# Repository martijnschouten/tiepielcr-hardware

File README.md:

# TiePieLCR hardware
Contains the design files of the TiePieLCR multi-frequency spectrometer front-end. The TiePieLCR consists of a TiePie engineering HS5 with custom PCB and a 3D printed case. The front-end contains an instrumentation amplifier to measure differential voltages, a transimpedance amplifier to measure currents and  voltage controlled current source to be able to do safe current controlled measurements on humans.

To make one of your own you can use the supplied gerber files to get a PCB fabricated. To make some improments to design you can open the schematic in Kicad. The STL's and Inventor files of the case for the electronics can also be found in this repository.

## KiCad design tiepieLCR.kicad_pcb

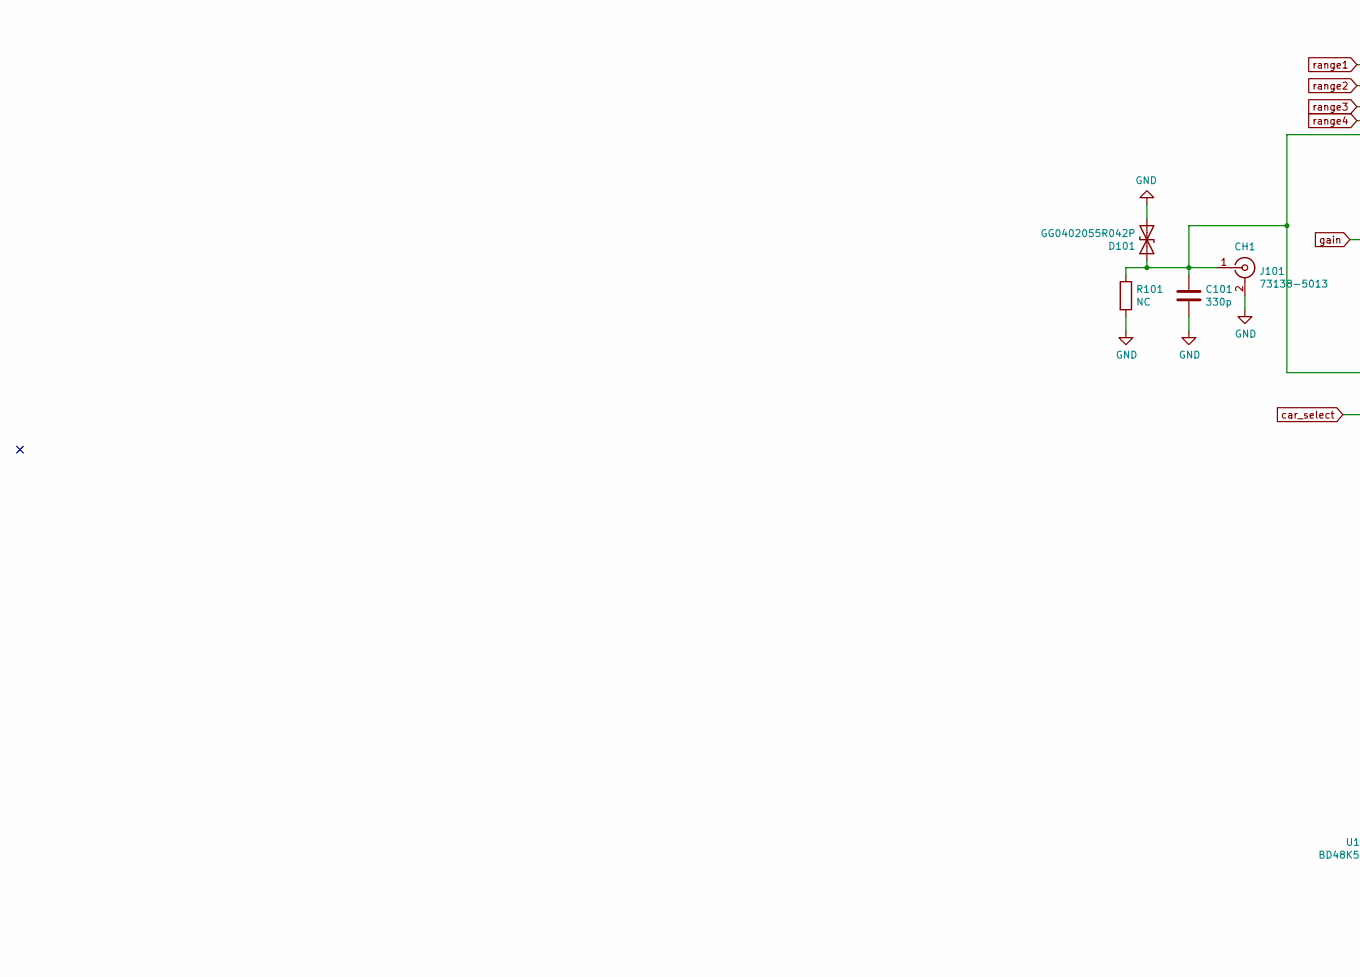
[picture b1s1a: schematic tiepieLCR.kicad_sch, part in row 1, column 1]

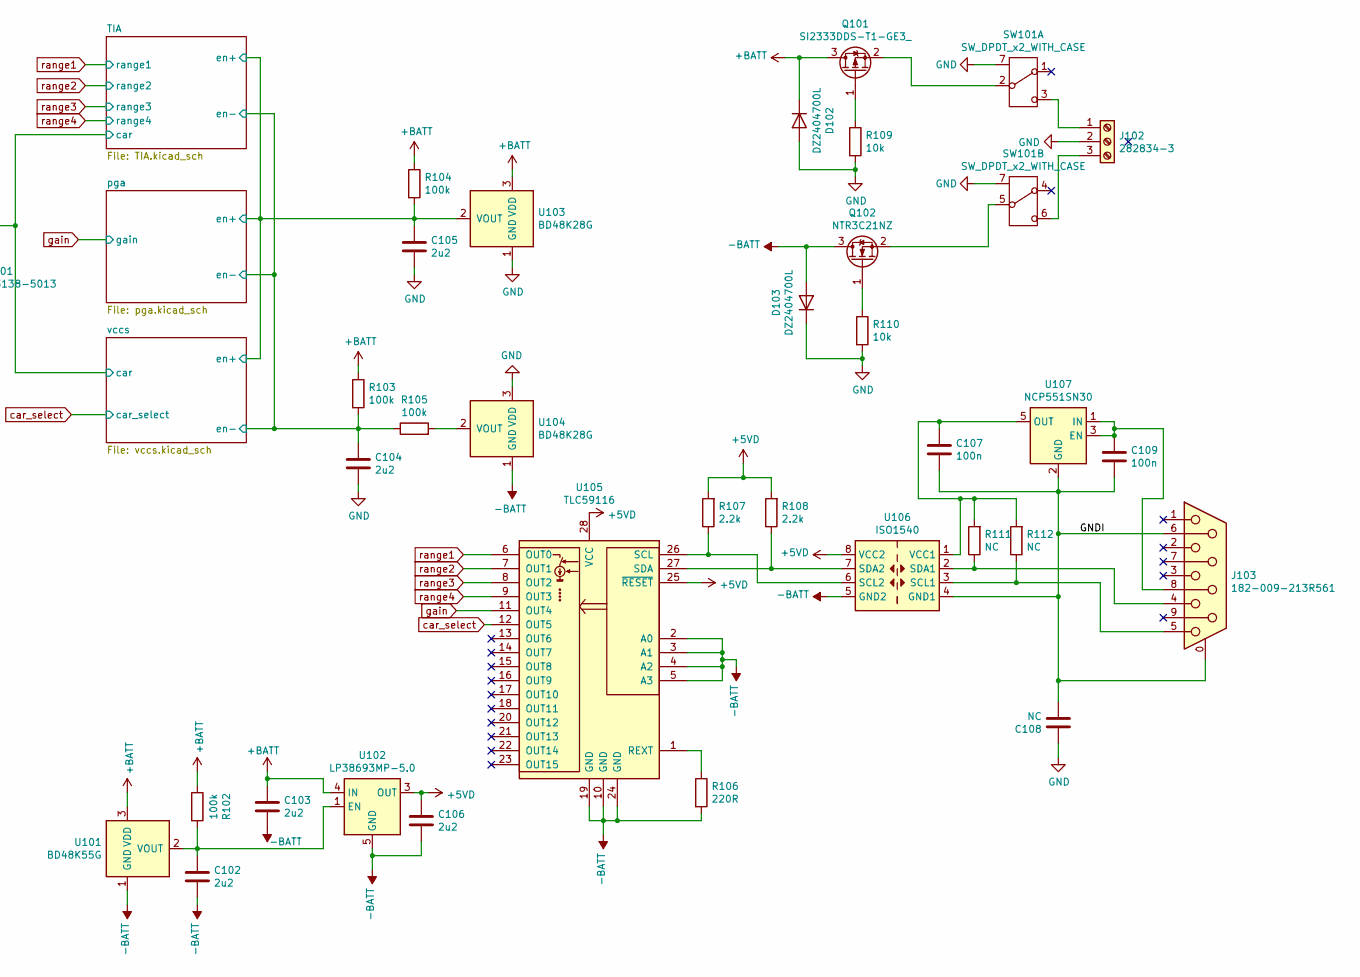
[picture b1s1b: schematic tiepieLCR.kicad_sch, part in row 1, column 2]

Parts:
C101: 330p; C_0603_1608Metric_Pad1.05x0.95mm_HandSolder
C102, C103, C104, C105, C106: 2u2; C_0603_1608Metric_Pad1.05x0.95mm_HandSolder
C107, C109: 100n; C_0603_1608Metric_Pad1.05x0.95mm_HandSolder
C108: NC; C_1206_3216Metric
D101: GG0402055R042P; D_0402_1005Metric
D102, D103: DZ2404700L; D_SOD-128
J101: 73138-5013; 0731385033
J102: 282834-3; TerminalBlock_TE_282834-3_1x03_P2.54mm_Horizontal
J103: 182-009-213R561; DSUB-9_Female_Horizontal_P2.77x2.84mm_EdgePinOffset7.70mm_H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
Q101: SI2333DDS-T1-GE3_; SOT-23
Q102: NTR3C21NZ; SOT-23
R101, R111, R112: NC; R_0603_1608Metric_Pad1.05x0.95mm_HandSolder
R102, R103, R104, R105: 100k; R_0603_1608Metric_Pad1.05x0.95mm_HandSolder
R106: 220R; R_0603_1608Metric_Pad1.05x0.95mm_HandSolder
R107, R108: 2.2k; R_0603_1608Metric_Pad1.05x0.95mm_HandSolder
R109, R110: 10k; R_0603_1608Metric_Pad1.05x0.95mm_HandSolder
SW101: SW_DPDT_x2_WITH_CASE; EG2219
U101: BD48K55G; SOT-23
U102: LP38693MP-5.0; SOT-223-5
U103, U104: BD48K28G; SOT-23
U105: TLC59116; TSSOP-28_4.4x9.7mm_P0.65mm
U106: ISO1540; SOIC-8_3.9x4.9mm_P1.27mm
U107: NCP551SN30; SOT-23-5

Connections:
+5VD: C106.1, R107.2, R108.2, U102.3 (OUT), U105.25 (~RESET), U105.28 (VCC), U106.8 (VCC2); also elsewhere on the board
+BATT: C103.1, D102.1 (K), Q101.3 (D), R102.1, R103.1, R104.1, U101.3 (VDD), U102.4 (IN), U103.3 (VDD); also elsewhere on the board
-BATT: C102.2, C103.2, C106.2, D103.2 (A), Q102.3 (D), R106.2, U101.1 (GND), U102.5 (GND), U104.1 (GND), U105.2 (A0), U105.3 (A1), U105.4 (A2), U105.5 (A3), U105.10 (GND), U105.19 (GND), U105.24 (GND), U106.5 (GND2); also elsewhere on the board
/GNDI: C107.2, C108.2, C109.2, J103.0 (PAD), J103.6 (GND), U106.4 (GND1), U107.2 (GND)
/TIA/car: C101.1, D101.1 (A1), J101.1 (In), R101.1; also elsewhere on the board
/TIA/en+: C105.1, R104.2, U103.2 (VOUT); also elsewhere on the board
/TIA/en-: C104.1, R103.2, R105.1; also elsewhere on the board
GND: C101.2, C104.2, C105.2, C108.1, D101.2 (A2), D102.2 (A), D103.1 (K), J101.2 (Ext), J102.2, R101.2, R109.2, R110.2, SW101.7 (CASE), U103.1 (GND), U104.3 (VDD); also elsewhere on the board
unnamed: C102.1, R102.2, U101.2 (VOUT), U102.1 (EN)
unnamed: C107.1, R111.2, R112.2, U106.1 (VCC1), U107.5 (OUT)
unnamed: C109.1, J103.8 (OUT), U107.1 (IN), U107.3 (EN)
unnamed: J102.1, SW101.3 (C)
unnamed: J102.3, SW101.6 (C)
unnamed: J103.4 (SDA), R111.1, U106.2 (SDA1)
unnamed: J103.5 (SCL), R112.1, U106.3 (SCL1)
unnamed: Q101.1 (G), R109.1
unnamed: Q101.2 (S), SW101.2 (B)
unnamed: Q102.1 (G), R110.1
unnamed: Q102.2 (S), SW101.5 (B)
unnamed: R105.2, U104.2 (VOUT)
unnamed: R106.1, U105.1 (REXT)
unnamed: R107.1, U105.26 (SCL), U106.6 (SCL2)
unnamed: R108.1, U105.27 (SDA), U106.7 (SDA2)
car_select: U105.12 (OUT5); also elsewhere on the board
gain: U105.11 (OUT4); also elsewhere on the board
range1: U105.6 (OUT0); also elsewhere on the board
range2: U105.7 (OUT1); also elsewhere on the board
range3: U105.8 (OUT2); also elsewhere on the board
range4: U105.9 (OUT3); also elsewhere on the board

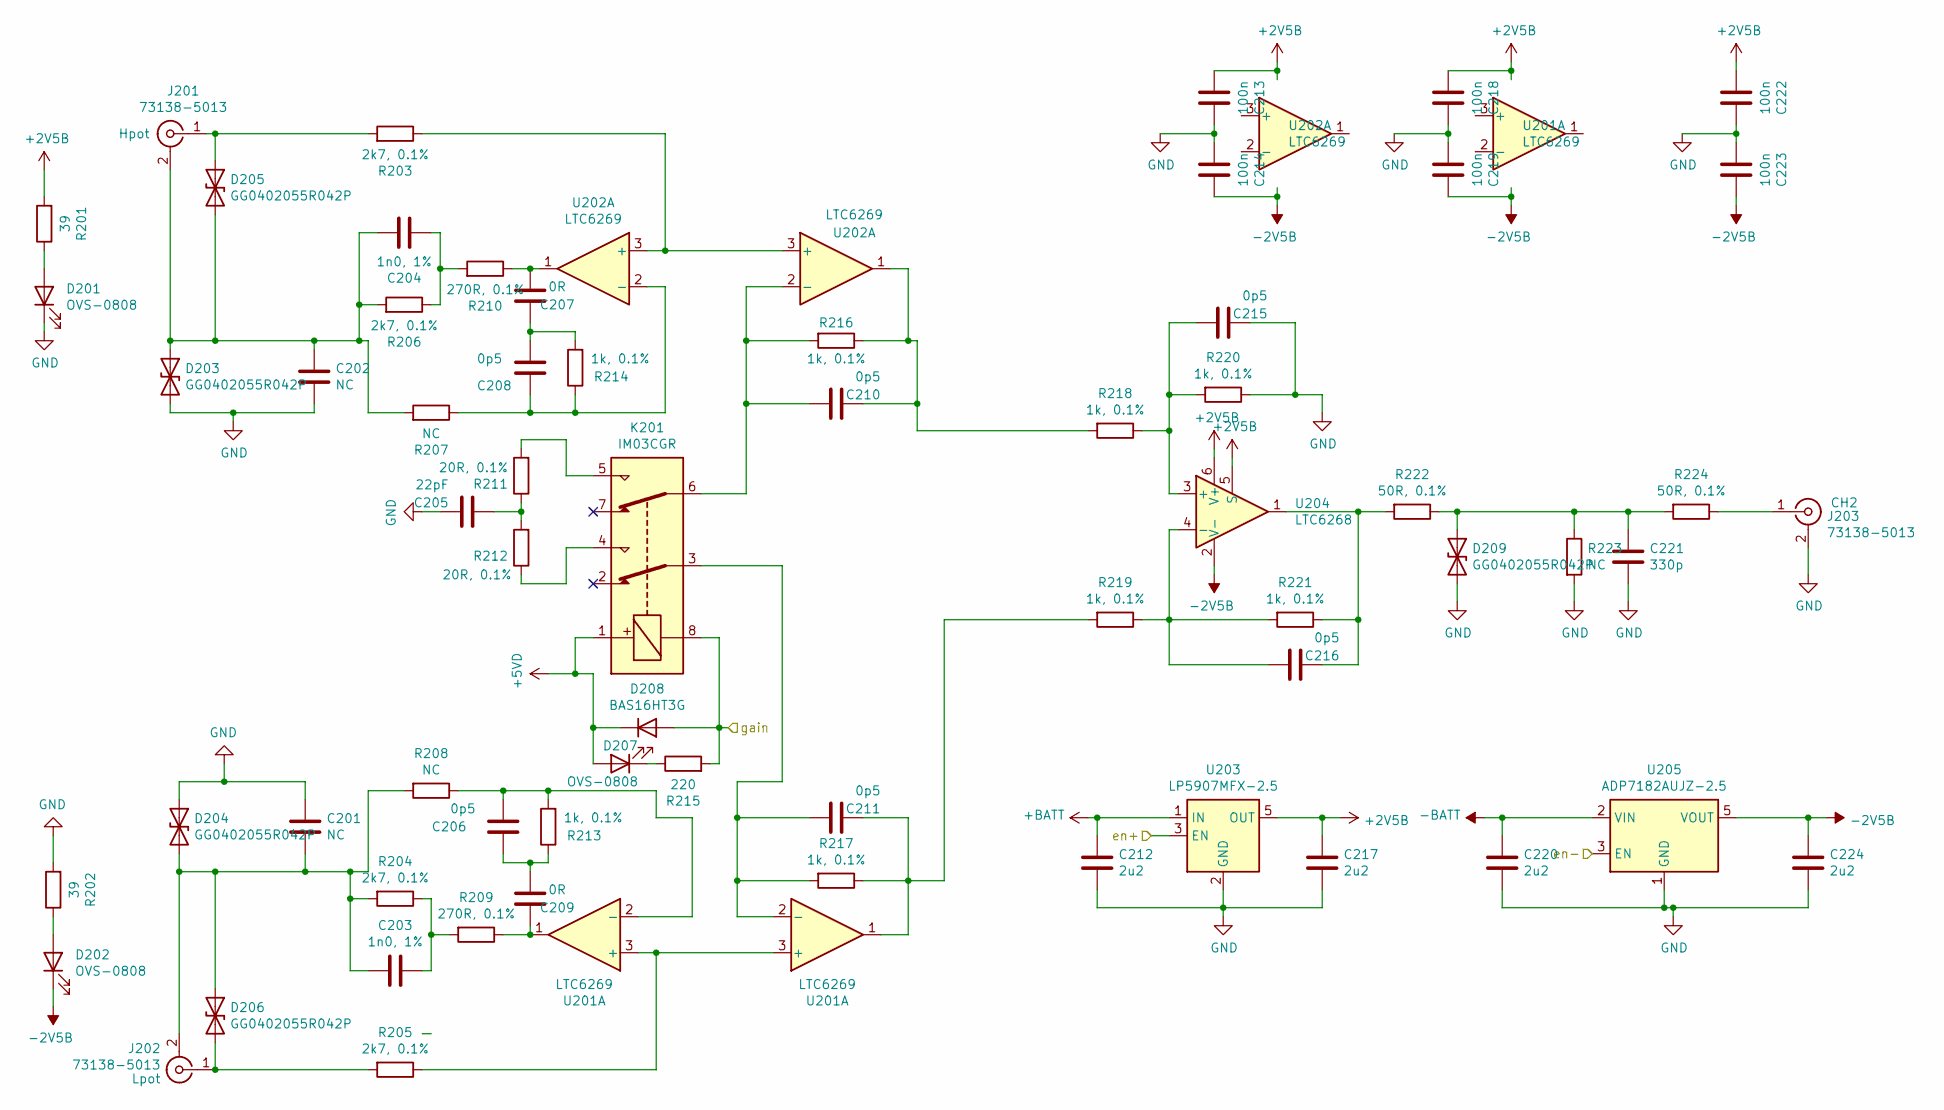
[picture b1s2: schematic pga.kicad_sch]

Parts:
C201, C202: NC; C_0603_1608Metric_Pad1.05x0.95mm_HandSolder
C203, C204: 1n0, 1%; C_0603_1608Metric_Pad1.05x0.95mm_HandSolder
C205: 22pF; C_0603_1608Metric_Pad1.05x0.95mm_HandSolder
C206, C208, C210, C211, C215, C216: 0p5; C_0603_1608Metric_Pad1.05x0.95mm_HandSolder
C207, C209: 0R; C_0603_1608Metric_Pad1.05x0.95mm_HandSolder
C212, C217, C220, C224: 2u2; C_0603_1608Metric_Pad1.05x0.95mm_HandSolder
C213, C214, C218, C219, C222, C223: 100n; C_0603_1608Metric_Pad1.05x0.95mm_HandSolder
C221: 330p; C_0603_1608Metric_Pad1.05x0.95mm_HandSolder
D201, D202, D207: OVS-0808; LED_0805_2012Metric
D203, D204, D205, D206, D209: GG0402055R042P; D_0402_1005Metric
D208: BAS16HT3G; D_SOD-323
J201, J202, J203: 73138-5013; 0731385033
K201: IM03CGR; 1462039-4
R201, R202: 39; R_0603_1608Metric_Pad1.05x0.95mm_HandSolder
R203, R204, R205, R206: 2k7, 0.1%; R_0603_1608Metric_Pad1.05x0.95mm_HandSolder
R207, R208, R223: NC; R_0603_1608Metric_Pad1.05x0.95mm_HandSolder
R209, R210: 270R, 0.1%; R_0603_1608Metric_Pad1.05x0.95mm_HandSolder
R211, R212: 20R, 0.1%; R_0603_1608Metric_Pad1.05x0.95mm_HandSolder
R213, R214, R216, R217, R218, R219, R220, R221: 1k, 0.1%; R_0603_1608Metric
R215: 220; R_0603_1608Metric_Pad1.05x0.95mm_HandSolder
R222, R224: 50R, 0.1%; R_0603_1608Metric
U201, U202: LTC6269; MSOP-8_3x3mm_P0.65mm
U203: LP5907MFX-2.5; SOT-23-5
U204: LTC6268; SOT-23-6_Handsoldering
U205: ADP7182AUJZ-2.5; TSOT-23-5

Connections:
+2V5B: C213.2, C217.2, C218.2, C222.2, R201.2, U201.8 (V+), U202.8 (V+), U203.5 (OUT), U204.5 (S), U204.6 (V+)
+5VD: D207.2 (A), D208.1 (K), K201.1; also elsewhere on the board
+BATT: C212.2, U203.1 (IN); also elsewhere on the board
-2V5B: C214.1, C219.1, C223.1, C224.2, D202.1 (K), U201.4 (V-), U202.4 (V-), U204.2 (V-), U205.5 (VOUT)
-BATT: C220.2, U205.2 (VIN); also elsewhere on the board
/TIA/en+: U203.3 (EN); also elsewhere on the board
/TIA/en-: U205.3 (EN); also elsewhere on the board
GND: C201.1, C202.2, C205.2, C212.1, C213.1, C214.2, C215.1, C217.1, C218.1, C219.2, C220.1, C221.2, C222.1, C223.2, C224.1, D201.1 (K), D203.2 (A2), D204.1 (A1), D209.2 (A2), J203.2 (Ext), R202.2, R220.1, R223.2, U203.2 (GND), U205.1 (GND); also elsewhere on the board
unnamed: C201.2, C203.2, D204.2 (A2), D206.1 (A1), J202.2 (Ext), R204.2, R208.2
unnamed: C202.1, C204.2, D203.1 (A1), D205.2 (A2), J201.2 (Ext), R206.2, R207.2
unnamed: C203.1, R204.1, R209.2
unnamed: C204.1, R206.1, R210.2
unnamed: C205.1, R211.1, R212.2
unnamed: C206.2, C209.2, R213.1
unnamed: C207.1, C208.1, R214.2
unnamed: C215.2, R218.1, R220.2, U204.3 (+)
unnamed: C216.1, R221.1, R222.2, U204.1
unnamed: C216.2, R219.1, R221.2, U204.4 (-)
unnamed: C221.1, D209.1 (A1), R222.1, R223.1, R224.2
unnamed: D201.2 (A), R201.1
unnamed: D202.2 (A), R202.1
unnamed: D205.1 (A1), J201.1 (In), R203.2
unnamed: D206.2 (A2), J202.1 (In), R205.2
unnamed: D207.1 (K), R215.1
unnamed: J203.1 (In), R224.1
unnamed: K201.4, R212.1
unnamed: K201.5, R211.2
unnamed: R203.1, U202.3 (+), U202.5 (+)
unnamed: R205.1, U201.3 (+), U201.5 (+)
gain: D208.2 (A), K201.8, R215.2; also elsewhere on the board

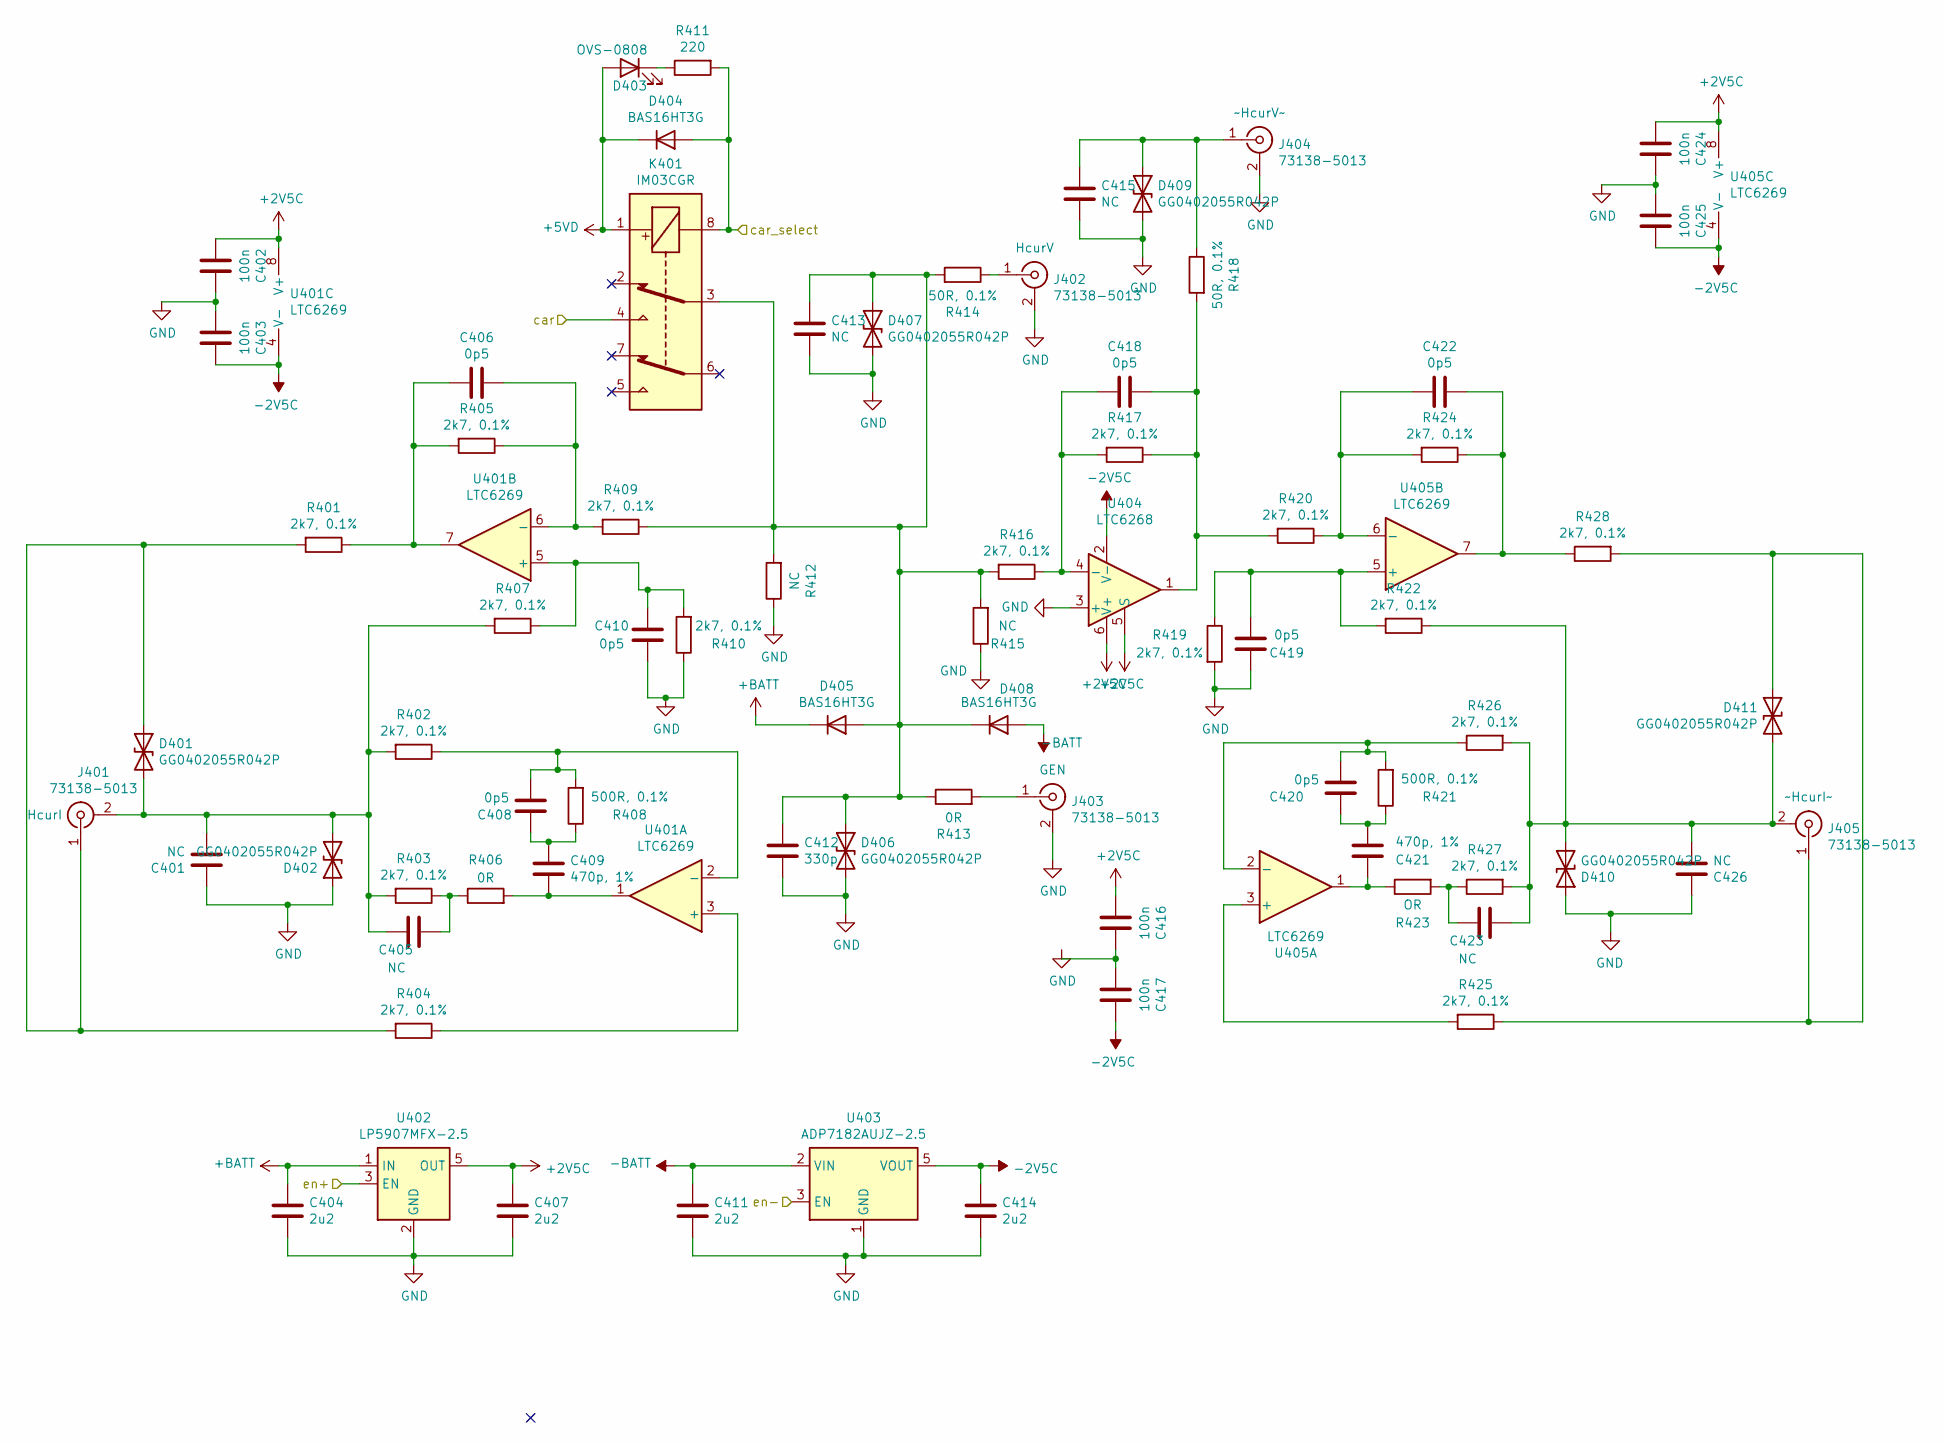
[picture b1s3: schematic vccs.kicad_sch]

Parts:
C401, C405, C413, C415, C423, C426: NC; C_0603_1608Metric_Pad1.05x0.95mm_HandSolder
C402, C403, C416, C417, C424, C425: 100n; C_0603_1608Metric_Pad1.05x0.95mm_HandSolder
C404, C407, C411, C414: 2u2; C_0603_1608Metric_Pad1.05x0.95mm_HandSolder
C406, C408, C410, C418, C419, C420, C422: 0p5; C_0603_1608Metric_Pad1.05x0.95mm_HandSolder
C409, C421: 470p, 1%; C_0603_1608Metric_Pad1.05x0.95mm_HandSolder
C412: 330p; C_0603_1608Metric_Pad1.05x0.95mm_HandSolder
D401, D402, D406, D407, D409, D410, D411: GG0402055R042P; D_0402_1005Metric
D403: OVS-0808; LED_0805_2012Metric
D404, D405, D408: BAS16HT3G; D_SOD-323
J401, J402, J403, J404, J405: 73138-5013; 0731385033
K401: IM03CGR; 1462039-4
R401, R402, R403, R404, R405, R407, R409, R410, R416, R417, R419, R420, R422, R424, R425, R426, R427, R428: 2k7, 0.1%; R_0603_1608Metric_Pad1.05x0.95mm_HandSolder
R406, R413: 0R; R_0603_1608Metric_Pad1.05x0.95mm_HandSolder
R408, R421: 500R, 0.1%; R_0603_1608Metric_Pad1.05x0.95mm_HandSolder
R411: 220; R_0603_1608Metric_Pad1.05x0.95mm_HandSolder
R412, R415: NC; R_0603_1608Metric_Pad1.05x0.95mm_HandSolder
R414, R418: 50R, 0.1%; R_0603_1608Metric
R423: OR; R_0603_1608Metric_Pad1.05x0.95mm_HandSolder
U401, U405: LTC6269; MSOP-8_3x3mm_P0.65mm
U402: LP5907MFX-2.5; SOT-23-5
U403: ADP7182AUJZ-2.5; TSOT-23-5
U404: LTC6268; SOT-23-6_Handsoldering

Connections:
+2V5C: C402.2, C407.2, C416.2, C424.2, U401.8 (V+), U402.5 (OUT), U404.5 (S), U404.6 (V+), U405.8 (V+)
+5VD: D403.2 (A), D404.1 (K), K401.1; also elsewhere on the board
+BATT: C404.2, D405.1 (K), U402.1 (IN); also elsewhere on the board
-2V5C: C403.1, C414.2, C417.1, C425.1, U401.4 (V-), U403.5 (VOUT), U404.2 (V-), U405.4 (V-)
-BATT: C411.2, D408.2 (A), U403.2 (VIN); also elsewhere on the board
/TIA/car: K401.4; also elsewhere on the board
/TIA/en+: U402.3 (EN); also elsewhere on the board
/TIA/en-: U403.3 (EN); also elsewhere on the board
GND: C401.1, C402.1, C403.2, C404.1, C407.1, C410.2, C411.1, C412.1, C413.1, C414.1, C415.1, C419.2, C424.1, C425.2, C426.1, D402.1 (A1), D406.2 (A2), D407.2 (A2), D409.2 (A2), D410.1 (A1), J402.2 (Ext), J403.2 (Ext), J404.2 (Ext), R410.1, R412.1, R415.1, R419.2, U402.2 (GND), U403.1 (GND), U404.3 (+); also elsewhere on the board
unnamed: C401.2, C405.1, D401.2 (A2), D402.2 (A2), J401.2 (Ext), R402.2, R403.2, R407.2
unnamed: C405.2, R403.1, R406.1
unnamed: C406.1, R405.1, R409.2, U401.6 (-)
unnamed: C406.2, R401.1, R405.2, U401.7
unnamed: C408.1, R402.1, R408.2, U401.2 (-)
unnamed: C408.2, C409.2, R408.1
unnamed: C409.1, R406.2, U401.1
unnamed: C410.1, R407.1, R410.2, U401.5 (+)
unnamed: C412.2, C413.2, D405.2 (A), D406.1 (A1), D407.1 (A1), D408.1 (K), K401.3, R409.1, R412.2, R413.1, R414.2, R415.2, R416.2
unnamed: C415.2, D409.1 (A1), J404.1 (In), R418.1
unnamed: C416.1, C417.2
unnamed: C418.1, R417.1, R418.2, R420.2, U404.1
unnamed: C418.2, R416.1, R417.2, U404.4 (-)
unnamed: C419.1, R419.1, R422.2, U405.5 (+)
unnamed: C420.1, R421.2, R426.1, U405.2 (-)
unnamed: C420.2, C421.2, R421.1
unnamed: C421.1, R423.1, U405.1
unnamed: C422.1, R420.1, R424.2, U405.6 (-)
unnamed: C422.2, R424.1, R428.1, U405.7
unnamed: C423.1, R423.2, R427.1
unnamed: C423.2, C426.2, D410.2 (A2), D411.2 (A2), J405.2 (Ext), R422.1, R426.2, R427.2
unnamed: D401.1 (A1), J401.1 (In), R401.2, R404.2
unnamed: D403.1 (K), R411.1
unnamed: D411.1 (A1), J405.1 (In), R425.1, R428.2
unnamed: J402.1 (In), R414.1
unnamed: J403.1 (In), R413.2
unnamed: R404.1, U401.3 (+)
unnamed: R425.2, U405.3 (+)
car_select: D404.2 (A), K401.8, R411.2; also elsewhere on the board

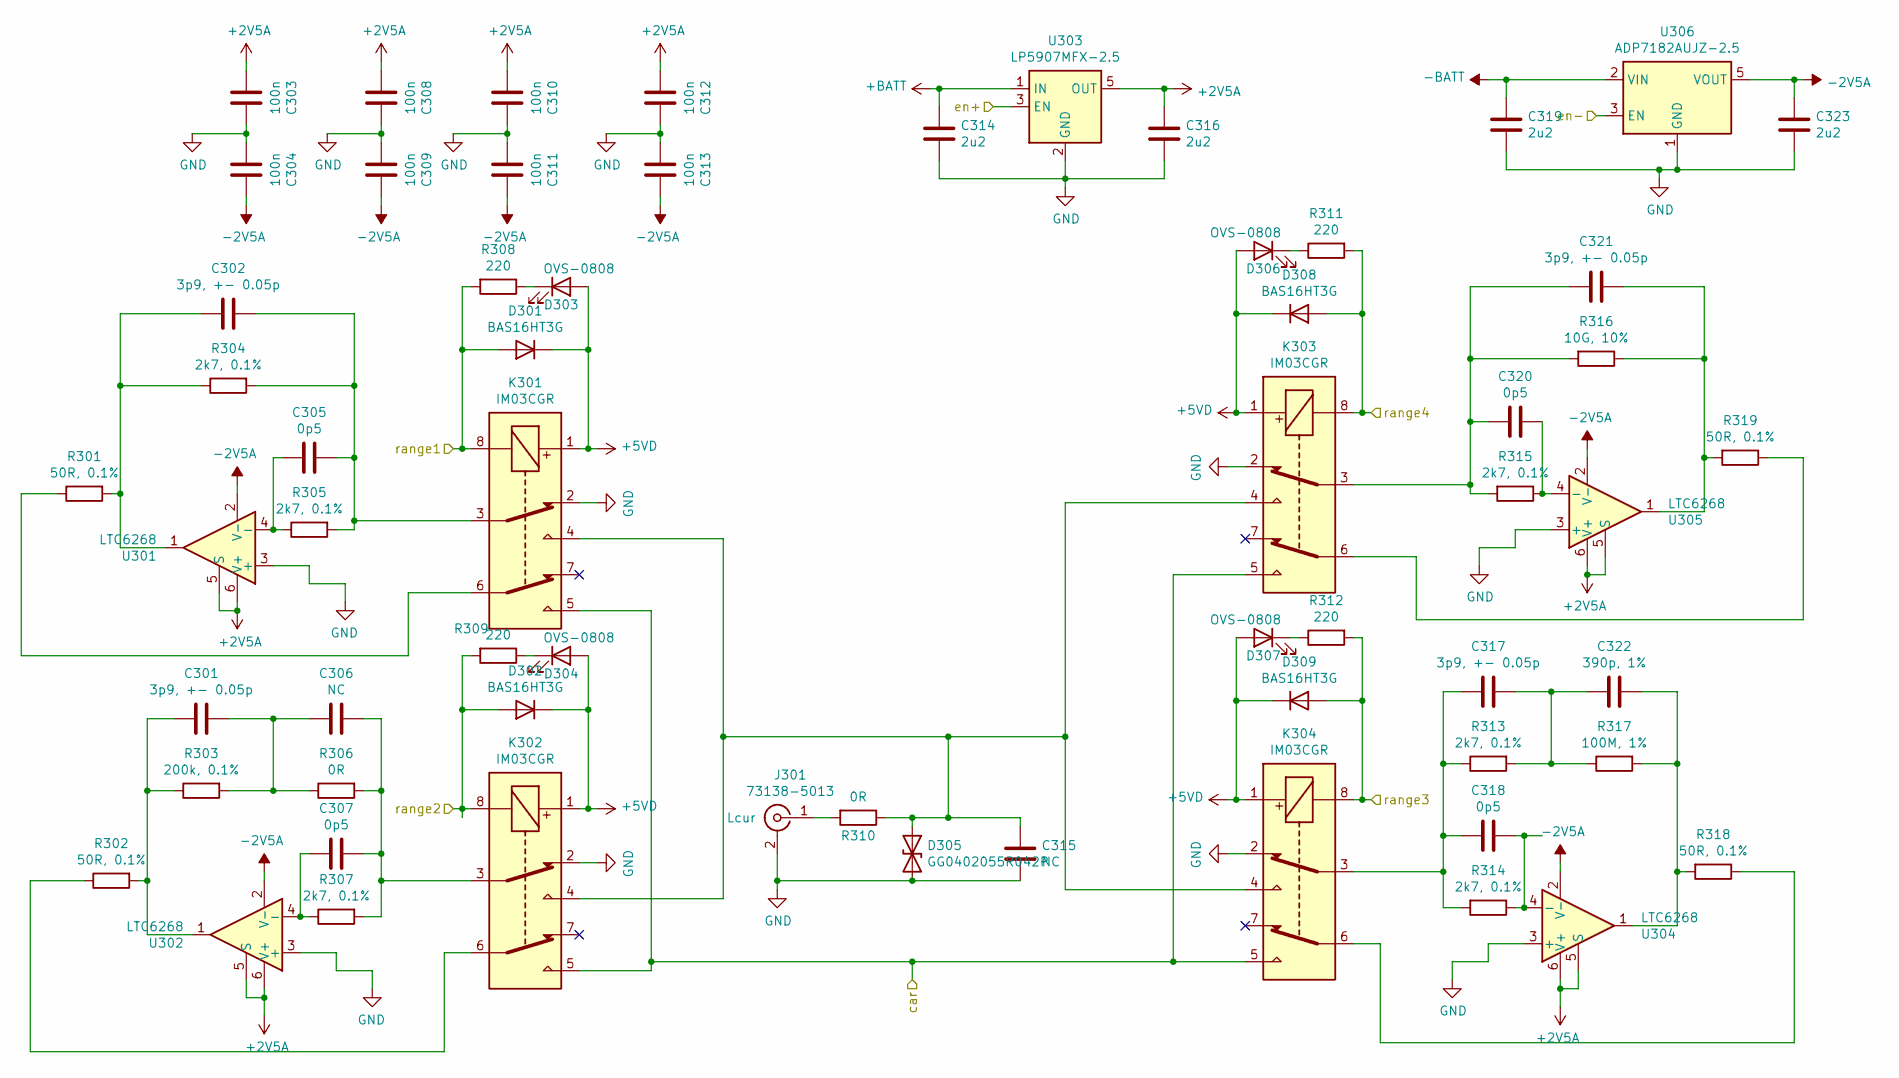
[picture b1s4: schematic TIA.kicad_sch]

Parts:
C301, C302, C317, C321: 3p9, +- 0.05p; C_0603_1608Metric_Pad1.05x0.95mm_HandSolder
C303, C304, C308, C309, C310, C311, C312, C313: 100n; C_0603_1608Metric_Pad1.05x0.95mm_HandSolder
C305, C307, C318, C320: 0p5; C_0603_1608Metric_Pad1.05x0.95mm_HandSolder
C306, C315: NC; C_0603_1608Metric_Pad1.05x0.95mm_HandSolder
C314, C316, C319, C323: 2u2; C_0603_1608Metric_Pad1.05x0.95mm_HandSolder
C322: 390p, 1%; C_0603_1608Metric_Pad1.05x0.95mm_HandSolder
D301, D302, D308, D309: BAS16HT3G; D_SOD-323
D303, D304, D306, D307: OVS-0808; LED_0805_2012Metric
D305: GG0402055R042P; D_0402_1005Metric
J301: 73138-5013; 0731385033
K301, K302, K303, K304: IM03CGR; 1462039-4
R301, R302, R318, R319: 50R, 0.1%; R_0603_1608Metric
R303: 200k, 0.1%; R_1206_3216Metric_Pad1.42x1.75mm_HandSolder
R304, R305, R307, R313, R314, R315: 2k7, 0.1%; R_0603_1608Metric_Pad1.05x0.95mm_HandSolder
R306, R310: 0R; R_0603_1608Metric_Pad1.05x0.95mm_HandSolder
R308, R309, R311, R312: 220; R_0603_1608Metric_Pad1.05x0.95mm_HandSolder
R316: 10G, 10%; R_1206_3216Metric_Pad1.42x1.75mm_HandSolder
R317: 100M, 1%; R_1206_3216Metric_Pad1.42x1.75mm_HandSolder
U301, U302, U304, U305: LTC6268; SOT-23-6_Handsoldering
U303: LP5907MFX-2.5; SOT-23-5
U306: ADP7182AUJZ-2.5; TSOT-23-5

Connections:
+2V5A: C303.2, C308.2, C310.2, C312.2, C316.2, U301.5 (S), U301.6 (V+), U302.5 (S), U302.6 (V+), U303.5 (OUT), U304.5 (S), U304.6 (V+), U305.5 (S), U305.6 (V+)
+5VD: D301.1 (K), D302.1 (K), D303.2 (A), D304.2 (A), D306.2 (A), D307.2 (A), D308.1 (K), D309.1 (K), K301.1, K302.1, K303.1, K304.1; also elsewhere on the board
+BATT: C314.2, U303.1 (IN); also elsewhere on the board
-2V5A: C304.1, C309.1, C311.1, C313.1, C323.2, U301.2 (V-), U302.2 (V-), U304.2 (V-), U305.2 (V-), U306.5 (VOUT)
-BATT: C319.2, U306.2 (VIN); also elsewhere on the board
/TIA/car: K301.5, K302.5, K303.5, K304.5; also elsewhere on the board
/TIA/en+: U303.3 (EN); also elsewhere on the board
/TIA/en-: U306.3 (EN); also elsewhere on the board
GND: C303.1, C304.2, C308.1, C309.2, C310.1, C311.2, C312.1, C313.2, C314.1, C315.2, C316.1, C319.1, C323.1, D305.2 (A2), J301.2 (Ext), K301.2, K302.2, K303.2, K304.2, U301.3 (+), U302.3 (+), U303.2 (GND), U304.3 (+), U305.3 (+), U306.1 (GND); also elsewhere on the board
unnamed: C301.1, R302.2, R303.1, U302.1
unnamed: C301.2, C306.1, R303.2, R306.1
unnamed: C302.1, R301.2, R304.1, U301.1
unnamed: C302.2, C305.2, K301.3, R304.2, R305.2
unnamed: C305.1, R305.1, U301.4 (-)
unnamed: C306.2, C307.2, K302.3, R306.2, R307.2
unnamed: C307.1, R307.1, U302.4 (-)
unnamed: C315.1, D305.1 (A1), K301.4, K302.4, K303.4, K304.4, R310.1
unnamed: C317.1, C318.1, K304.3, R313.1, R314.2
unnamed: C317.2, C322.1, R313.2, R317.1
unnamed: C318.2, R314.1, U304.4 (-)
unnamed: C320.1, C321.2, K303.3, R315.2, R316.2
unnamed: C320.2, R315.1, U305.4 (-)
unnamed: C321.1, R316.1, R319.2, U305.1
unnamed: C322.2, R317.2, R318.2, U304.1
unnamed: D303.1 (K), R308.1
unnamed: D304.1 (K), R309.1
unnamed: D306.1 (K), R311.1
unnamed: D307.1 (K), R312.1
unnamed: J301.1 (In), R310.2
unnamed: K301.6, R301.1
unnamed: K302.6, R302.1
unnamed: K303.6, R319.1
unnamed: K304.6, R318.1
range1: D301.2 (A), K301.8, R308.2; also elsewhere on the board
range2: D302.2 (A), K302.8, R309.2; also elsewhere on the board
range3: D309.2 (A), K304.8, R312.2; also elsewhere on the board
range4: D308.2 (A), K303.8, R311.2; also elsewhere on the board

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
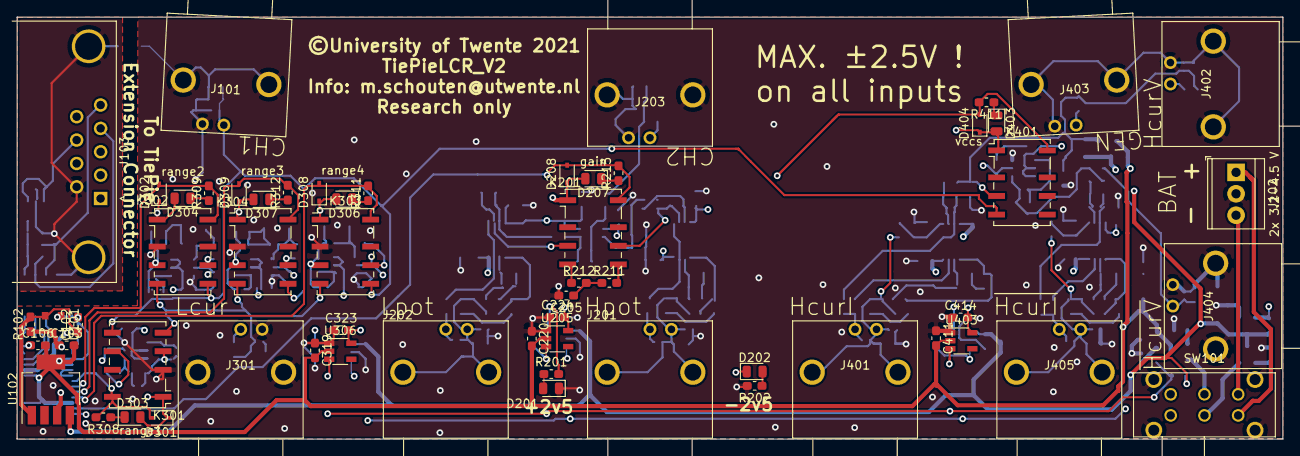
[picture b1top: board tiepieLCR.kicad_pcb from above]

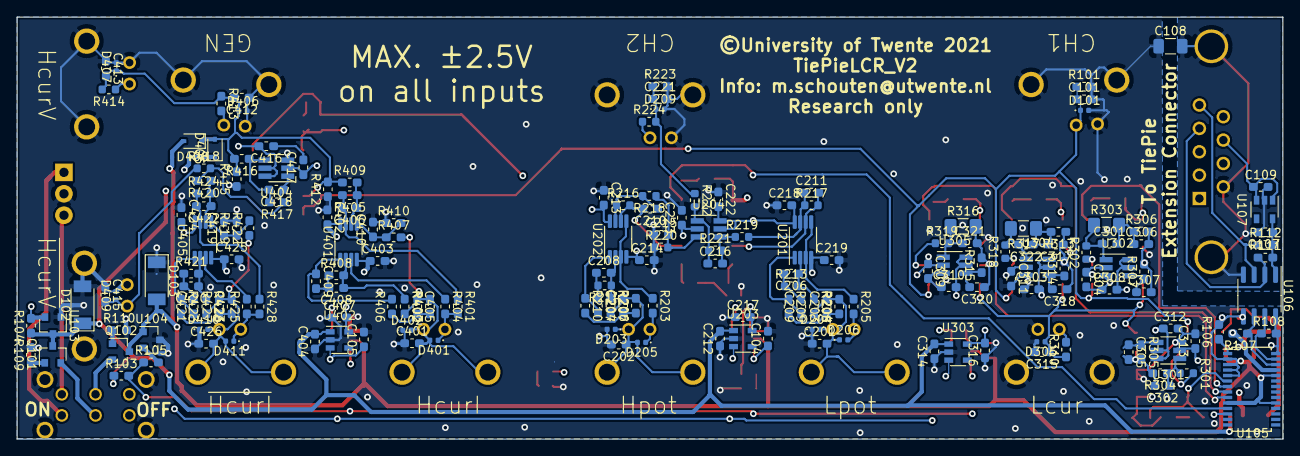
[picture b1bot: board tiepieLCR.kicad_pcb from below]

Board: 4 copper layers, 150.0 x 50.0 mm, 241 parts (182 on the bottom side), 116 nets.

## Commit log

2023-01-18 added cad files
2023-01-18 added casing

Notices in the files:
tiepieLCR.kicad_pcb:
©University of Twente 2021
